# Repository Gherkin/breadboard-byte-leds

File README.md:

# breadboard-byte-leds
a small board for mounting in breadboards and showing 2x9 bits (1 byte plus carry)  
ibom: https://gherkin.github.io/breadboard-byte-leds/

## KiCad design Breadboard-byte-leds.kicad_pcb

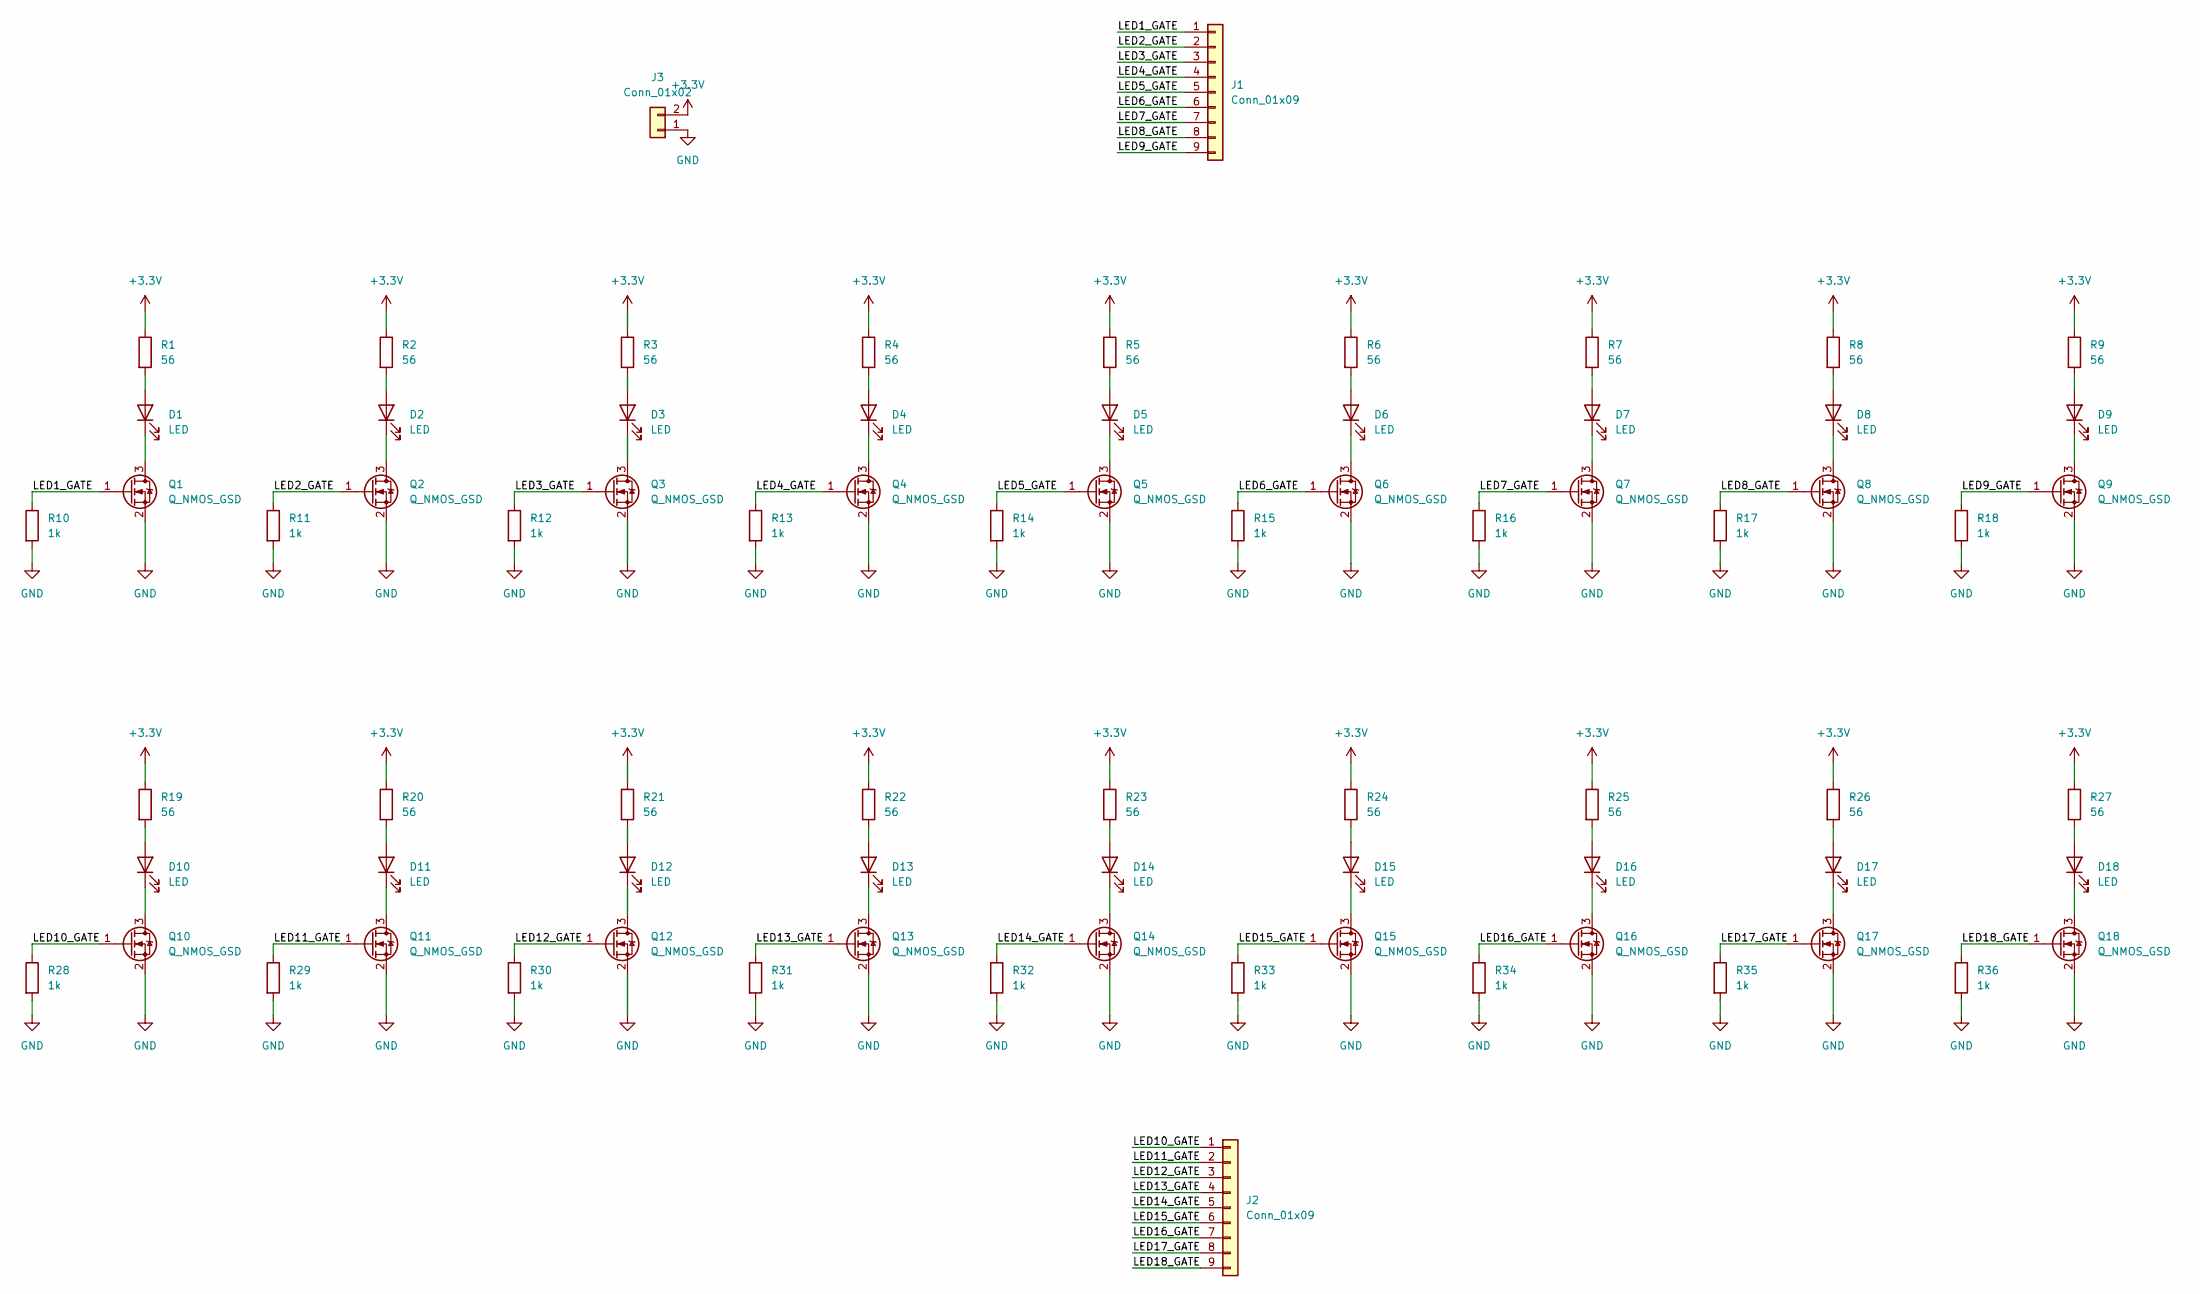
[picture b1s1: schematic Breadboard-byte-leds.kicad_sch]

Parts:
D1, D2, D3, D4, D5, D6, D7, D8, D9, D10, D11, D12, D13, D14, D15, D16, D17, D18: LED; LED_0603_1608Metric; LCSC C965798
J1, J2: Conn_01x09; PinHeader_1x09_P2.54mm_Vertical
J3: Conn_01x02; PinHeader_1x02_P2.54mm_Vertical
Q1, Q2, Q3, Q4, Q5, Q6, Q7, Q8, Q9, Q10, Q11, Q12, Q13, Q14, Q15, Q16, Q17, Q18: Q_NMOS_GSD; SOT-23; LCSC C2874697
R1, R2, R3, R4, R5, R6, R7, R8, R9, R19, R20, R21, R22, R23, R24, R25, R26, R27: 56; R_0402_1005Metric; LCSC C25173
R10, R11, R12, R13, R14, R15, R16, R17, R18, R28, R29, R30, R31, R32, R33, R34, R35, R36: 1k; R_0402_1005Metric; LCSC C25543

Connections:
+3.3V: J3.2, R1.1, R2.1, R3.1, R4.1, R5.1, R6.1, R7.1, R8.1, R9.1, R19.1, R20.1, R21.1, R22.1, R23.1, R24.1, R25.1, R26.1, R27.1
/LED1_GATE: J1.1, Q1.1 (G), R10.1
/LED2_GATE: J1.2, Q2.1 (G), R11.1
/LED3_GATE: J1.3, Q3.1 (G), R12.1
/LED4_GATE: J1.4, Q4.1 (G), R13.1
/LED5_GATE: J1.5, Q5.1 (G), R14.1
/LED6_GATE: J1.6, Q6.1 (G), R15.1
/LED7_GATE: J1.7, Q7.1 (G), R16.1
/LED8_GATE: J1.8, Q8.1 (G), R17.1
/LED9_GATE: J1.9, Q9.1 (G), R18.1
/LED10_GATE: J2.1, Q10.1 (G), R28.1
/LED11_GATE: J2.2, Q11.1 (G), R29.1
/LED12_GATE: J2.3, Q12.1 (G), R30.1
/LED13_GATE: J2.4, Q13.1 (G), R31.1
/LED14_GATE: J2.5, Q14.1 (G), R32.1
/LED15_GATE: J2.6, Q15.1 (G), R33.1
/LED16_GATE: J2.7, Q16.1 (G), R34.1
/LED17_GATE: J2.8, Q17.1 (G), R35.1
/LED18_GATE: J2.9, Q18.1 (G), R36.1
GND: J3.1, Q1.2 (S), Q2.2 (S), Q3.2 (S), Q4.2 (S), Q5.2 (S), Q6.2 (S), Q7.2 (S), Q8.2 (S), Q9.2 (S), Q10.2 (S), Q11.2 (S), Q12.2 (S), Q13.2 (S), Q14.2 (S), Q15.2 (S), Q16.2 (S), Q17.2 (S), Q18.2 (S), R10.2, R11.2, R12.2, R13.2, R14.2, R15.2, R16.2, R17.2, R18.2, R28.2, R29.2, R30.2, R31.2, R32.2, R33.2, R34.2, R35.2, R36.2
unnamed: D1.2 (A), R1.2
unnamed: D1.1 (K), Q1.3 (D)
unnamed: D2.2 (A), R2.2
unnamed: D2.1 (K), Q2.3 (D)
unnamed: D3.2 (A), R3.2
unnamed: D3.1 (K), Q3.3 (D)
unnamed: D4.2 (A), R4.2
unnamed: D4.1 (K), Q4.3 (D)
unnamed: D5.2 (A), R5.2
unnamed: D5.1 (K), Q5.3 (D)
unnamed: D6.2 (A), R6.2
unnamed: D6.1 (K), Q6.3 (D)
unnamed: D7.2 (A), R7.2
unnamed: D7.1 (K), Q7.3 (D)
unnamed: D8.2 (A), R8.2
unnamed: D8.1 (K), Q8.3 (D)
unnamed: D9.2 (A), R9.2
unnamed: D9.1 (K), Q9.3 (D)
unnamed: D10.2 (A), R19.2
unnamed: D10.1 (K), Q10.3 (D)
unnamed: D11.2 (A), R20.2
unnamed: D11.1 (K), Q11.3 (D)
unnamed: D12.2 (A), R21.2
unnamed: D12.1 (K), Q12.3 (D)
unnamed: D13.2 (A), R22.2
unnamed: D13.1 (K), Q13.3 (D)
unnamed: D14.2 (A), R23.2
unnamed: D14.1 (K), Q14.3 (D)
unnamed: D15.2 (A), R24.2
unnamed: D15.1 (K), Q15.3 (D)
unnamed: D16.2 (A), R25.2
unnamed: D16.1 (K), Q16.3 (D)
unnamed: D17.2 (A), R26.2
unnamed: D17.1 (K), Q17.3 (D)
unnamed: D18.2 (A), R27.2
unnamed: D18.1 (K), Q18.3 (D)

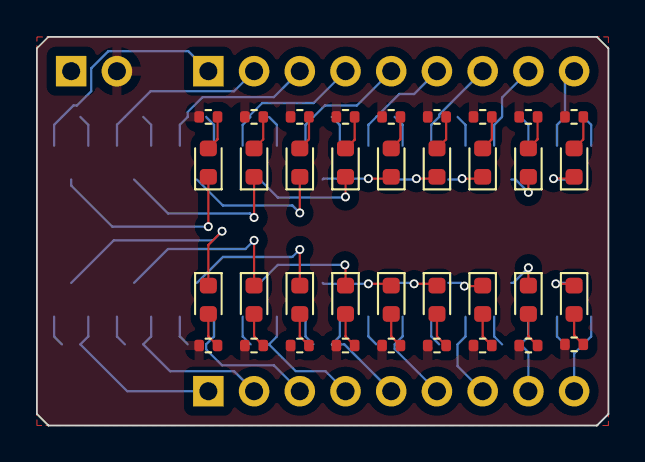
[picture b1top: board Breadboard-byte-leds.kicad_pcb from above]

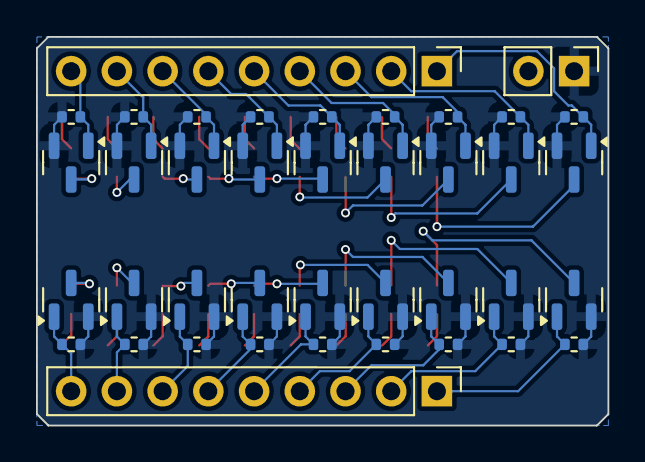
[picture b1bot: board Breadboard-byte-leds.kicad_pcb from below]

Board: 2 copper layers, 31.8 x 21.6 mm, 75 parts (39 on the bottom side), 56 nets.

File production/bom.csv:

Designator,Footprint,Quantity,Value,LCSC Part #
"D1, D10, D11, D12, D13, D14, D15, D16, D17, D18, D2, D3, D4, D5, D6, D7, D8, D9",0603,18,LED,C965798
"J1, J2",PinHeader_1x09_P2.54mm_Vertical,2,Conn_01x09,
J3,PinHeader_1x02_P2.54mm_Vertical,1,Conn_01x02,
"Q1, Q10, Q11, Q12, Q13, Q14, Q15, Q16, Q17, Q18, Q2, Q3, Q4, Q5, Q6, Q7, Q8, Q9",SOT-23,18,Q_NMOS_GSD,C2874697
"R1, R19, R2, R20, R21, R22, R23, R24, R25, R26, R27, R3, R4, R5, R6, R7, R8, R9",0402,18,56,C25173
"R10, R11, R12, R13, R14, R15, R16, R17, R18, R28, R29, R30, R31, R32, R33, R34, R35, R36",0402,18,1k,C25543

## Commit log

2024-05-22 init
2024-05-22 added picture
2024-05-22 added ibom html
2024-05-22 added ibom link
2024-05-22 wrong url
